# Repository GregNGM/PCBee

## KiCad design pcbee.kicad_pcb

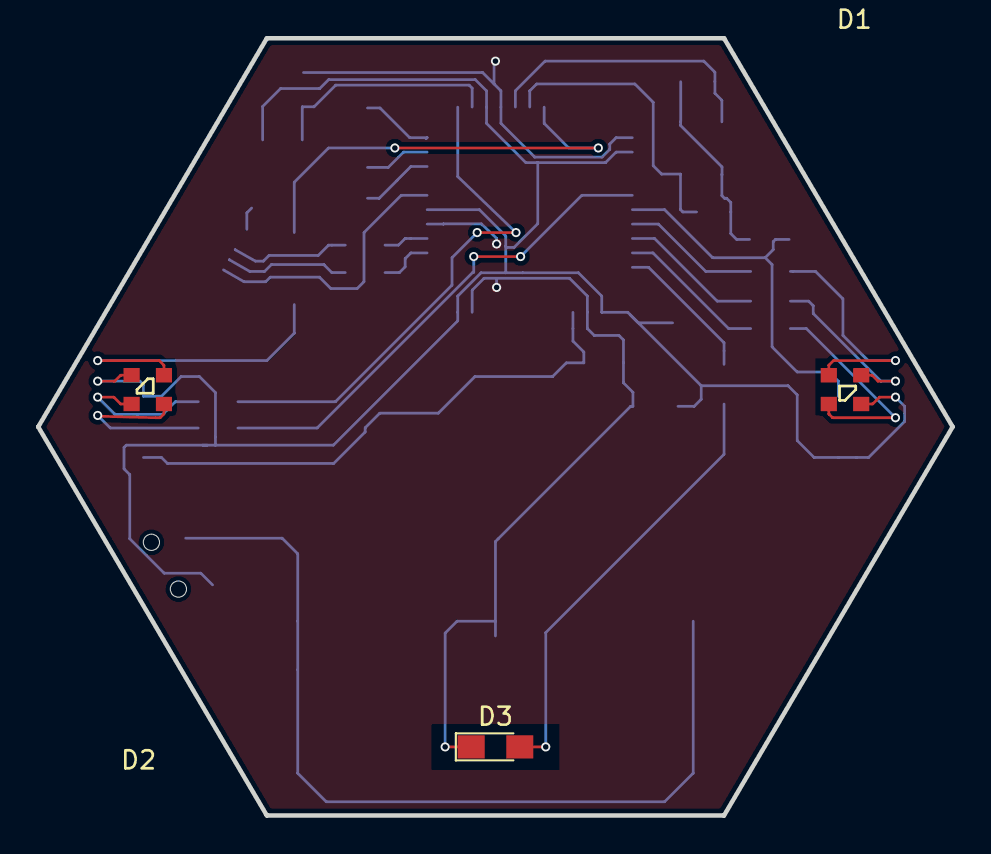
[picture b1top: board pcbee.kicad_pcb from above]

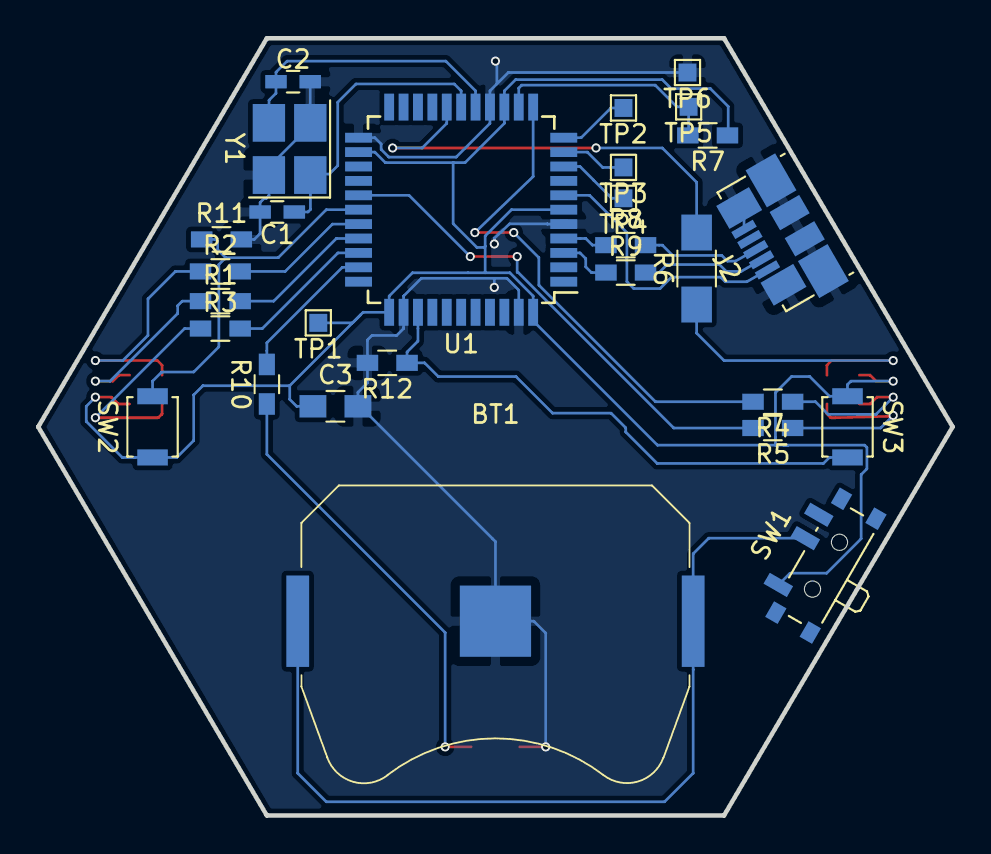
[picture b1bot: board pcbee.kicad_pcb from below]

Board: 2 copper layers, 50.8 x 43.2 mm, 31 parts (28 on the bottom side), 30 nets.

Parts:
BT1: Battery_Cell; Keystone_3034_1x20mm-CoinCell
C1, C2: 12pF; C_0603_HandSoldering
C3: 1u; C_0805_HandSoldering
D1, D2: ASMB-KTF0-0A306
D3: RED; LED_0805_HandSoldering
J2: USB_B_Micro; USB_Micro-B_Molex_47346-0001
R1, R2, R3, R4, R5: 330; R_0603_HandSoldering
R6: 330; R_1206_HandSoldering
R7: 10k; R_0603_HandSoldering
R8, R9: 22; R_0603_HandSoldering
R10: 470; R_0603_HandSoldering
R11, R12: 100k; R_0603_HandSoldering
SW1: SW_SPDT; SW_SPDT_PCM12
SW2: RIGHT; SW_SPST_B3U-1000P
SW3: LEFT; SW_SPST_B3U-1000P
TP1: Vdd; Test_Point_Pad_1.0x1.0mm
TP2: MISO; Test_Point_Pad_1.0x1.0mm
TP3: MOSI; Test_Point_Pad_1.0x1.0mm
TP4: CLK; Test_Point_Pad_1.0x1.0mm
TP5: RST; Test_Point_Pad_1.0x1.0mm
TP6: GND; Test_Point_Pad_1.0x1.0mm
U1: ATmega32U4-AU; TQFP-44_10x10mm_Pitch0.8mm
Y1: 16MHz; Crystal_SMD_3225-4pin_3.2x2.5mm_HandSoldering

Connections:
/LED: R10.2, U1.32
/RST: R7.2, TP5.1, U1.13
GND: BT1.2, C1.2, C2.2, C3.2, D3.1, J2.5, J2.6, R11.2, R12.2, TP6.1, U1.5, U1.15, U1.23, U1.35, U1.43, Y1.2, Y1.4
unnamed: BT1.1, SW1.2
unnamed: C1.1, U1.17, Y1.1
unnamed: C2.1, U1.16, Y1.3
unnamed: D1.2, R1.1
unnamed: D1.3, R2.1
unnamed: D1.4, R3.1
unnamed: D2.2, R4.1
unnamed: D2.3, R5.1
unnamed: D2.4, R6.1
unnamed: D3.2, R10.1
unnamed: J2.1, U1.7
unnamed: J2.2, R9.2
unnamed: J2.3, R8.2
unnamed: R1.2, U1.30
unnamed: R2.2, U1.29
unnamed: R3.2, U1.31
unnamed: R4.2, U1.12
unnamed: R5.2, U1.27
unnamed: R6.2, U1.18
unnamed: R8.1, U1.4
unnamed: R9.1, U1.3
unnamed: R11.1, SW2.2, U1.28
unnamed: R12.1, SW3.2, U1.36
unnamed: TP2.1, U1.11
unnamed: TP3.1, U1.10
unnamed: TP4.1, U1.9
VDD: C3.1, D1.1, D2.1, R7.1, SW1.1, SW2.1, SW3.1, TP1.1, U1.6, U1.14, U1.24, U1.34, U1.44

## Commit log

2018-04-07 Created Gerbers and checked
2018-07-04 Tidy up ready for Rev C design work
2018-07-09 Rev C intial design work
